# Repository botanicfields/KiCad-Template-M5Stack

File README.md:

# KiCad-Template-M5Stack
a PCB template of modules of M5Stack with footprints for KiCad.

## for KiCad 6
https://github.com/botanicfields/KiCad6-Environment

## for KiCad 5
- Manufacture with a thickness of 1.0 mm.
- M-BUS pin numbers match pin headers and pin sockets in the KiCad library.
- The template has a notch, but it may be actually needed only for the M5Stack controller board.

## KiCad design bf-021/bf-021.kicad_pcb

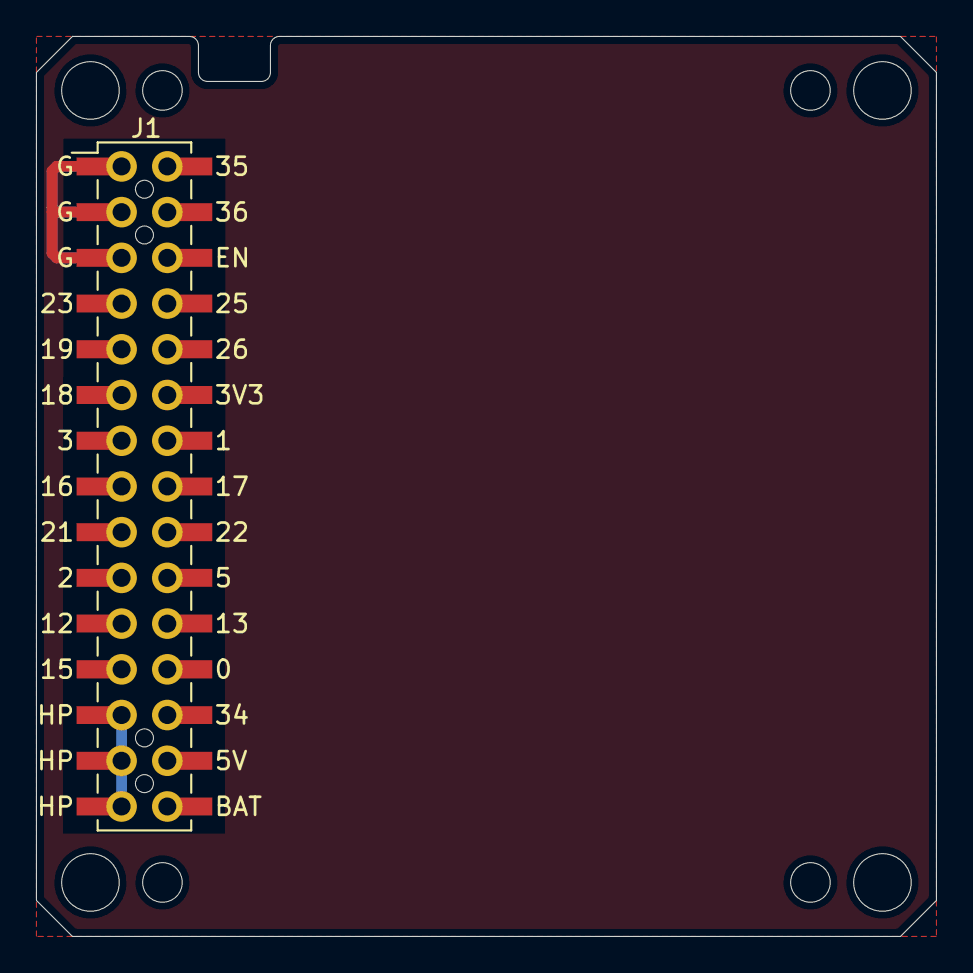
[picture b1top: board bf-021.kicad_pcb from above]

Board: 2 copper layers, 50.0 x 50.0 mm, 9 parts (0 on the bottom side), 2 nets.

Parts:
H1, H2, H3, H4: MountingHole; BF@MountingHole_3.2mm_M3
H5, H6, H7, H8: MountingHole; BF@MountingHole_2.2mm_M2
J1: M-BUS; BF@M5Stack_MBUS

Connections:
GND: J1.2, J1.4, J1.6
VBUS: J1.26, J1.28, J1.30

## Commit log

2021-06-10 V01L01
    the first upload
2021-06-11 V01L01
    replace
2021-06-12 image
    add image
2021-06-12 Update README.md
    thickness 1.0mm
2021-06-30 M-Bus footprint
    paste improved
2021-09-12 M-BUS connector
    update footprint
2022-02-05 refine drawing representations
    Correcting mistakes in chamfer dimension description values
    Change grid origin to center
    Added GPIO reference
2022-10-22 Update README.md
    link to KiCad6

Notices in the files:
bf-021/bf-021.kicad_pcb:
Copyright 2022 BotanicFields, Inc.
